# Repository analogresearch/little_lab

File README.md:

# LITTLE████_LAB

DC IN: 6..28 V 

MIDI noch noch nicht implementiert.

MIDI channel und Programm werden über Codierschalter gewählt.
MIDI: Ausnahme Schalter 0 = MIDI channel 16!

Rev.B: Pullups für Coderschalter
Rev.C: Pulldowns für inputs, debugging pads.

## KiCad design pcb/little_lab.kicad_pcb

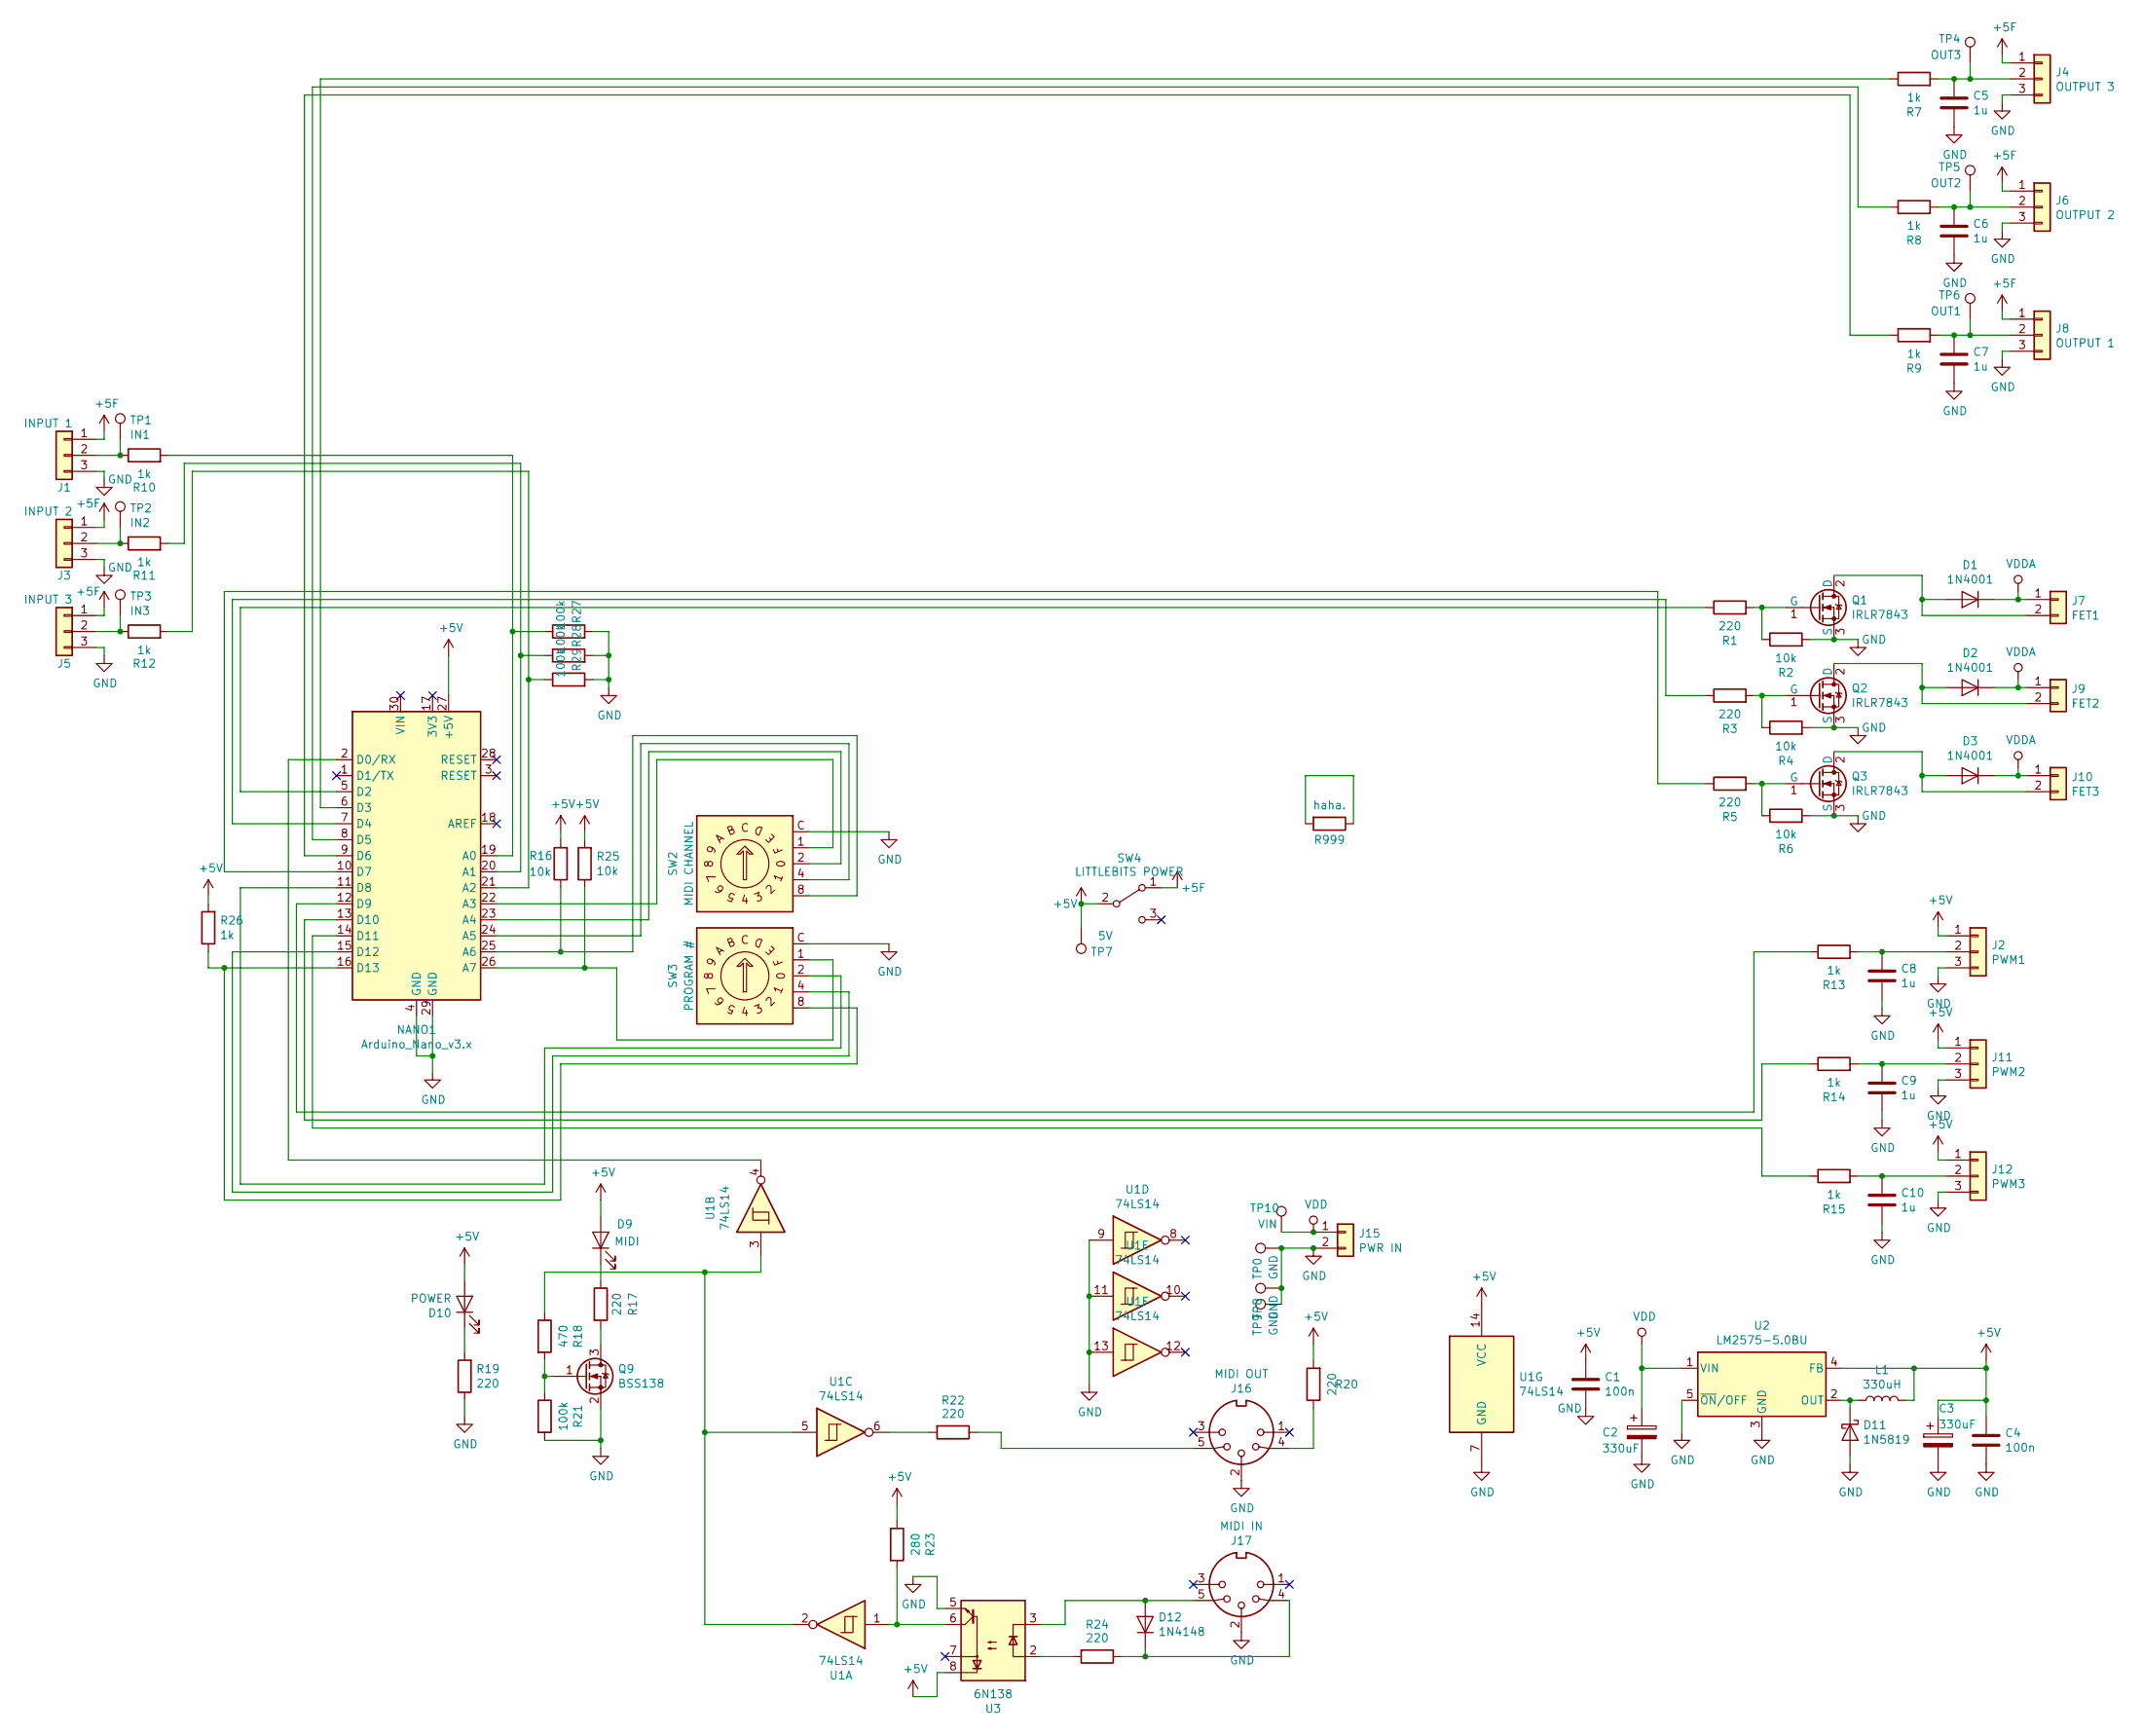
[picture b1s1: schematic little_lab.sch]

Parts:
C1, C4: 100n; C_1206_3216Metric_Pad1.42x1.75mm_HandSolder
C2, C3: 330uF; CP_Elec_10x10
C5, C6, C7, C8, C9, C10: 1u; C_1206_3216Metric_Pad1.42x1.75mm_HandSolder
D1, D2, D3: 1N4001; D_SOD-123F
D9: MIDI; LED_1206_3216Metric_Pad1.42x1.75mm_HandSolder
D10: POWER; LED_1206_3216Metric_Pad1.42x1.75mm_HandSolder
D11: 1N5819; D_SOD-123
D12: 1N4148; D_SOD-123
J1: INPUT 1; bitsnaps_input
J2: PWM1; EK508V-03P
J3: INPUT 2; bitsnaps_input
J4: OUTPUT 3; bitsnaps_output
J5: INPUT 3; bitsnaps_input
J6: OUTPUT 2; bitsnaps_output
J7: FET1; EK508V-02P
J8: OUTPUT 1; bitsnaps_output
J9: FET2; EK508V-02P
J10: FET3; EK508V-02P
J11: PWM2; EK508V-03P
J12: PWM3; EK508V-03P
J15: PWR IN; EK508V-02P
J16: MIDI OUT; MIDI_DIN5
J17: MIDI IN; MIDI_DIN5
L1: 330uH; L_7.3x7.3_Handsoldering
NANO1: Arduino_Nano_v3.x; Arduino_Nano
Q1, Q2, Q3: IRLR7843; TO-252-2
Q9: BSS138; SOT-23
R1, R3, R5, R17, R19, R20, R22, R24: 220; R_1206_3216Metric_Pad1.42x1.75mm_HandSolder
R2, R4, R6, R16, R25: 10k; R_1206_3216Metric_Pad1.42x1.75mm_HandSolder
R7, R8, R9, R10, R11, R12, R13, R14, R15, R26: 1k; R_1206_3216Metric_Pad1.42x1.75mm_HandSolder
R18: 470; R_1206_3216Metric_Pad1.42x1.75mm_HandSolder
R21, R27, R28, R29: 100k; R_1206_3216Metric_Pad1.42x1.75mm_HandSolder
R23: 280; R_1206_3216Metric_Pad1.42x1.75mm_HandSolder
R999: haha.; R_1206_3216Metric_Pad1.42x1.75mm_HandSolder
SW2: MIDI CHANNEL; SA-7050B
SW3: PROGRAM #; SA-7050B
SW4: LITTLEBITS POWER; K3-1235S-K1
TP0: GND; TestPoint_THTPad_D2.0mm_Drill1.0mm
TP1: IN1; TestPoint_THTPad_D2.0mm_Drill1.0mm
TP2: IN2; TestPoint_THTPad_D2.0mm_Drill1.0mm
TP3: IN3; TestPoint_THTPad_D2.0mm_Drill1.0mm
TP4: OUT3; TestPoint_THTPad_D2.0mm_Drill1.0mm
TP5: OUT2; TestPoint_THTPad_D2.0mm_Drill1.0mm
TP6: OUT1; TestPoint_THTPad_D2.0mm_Drill1.0mm
TP7: 5V; TestPoint_THTPad_D2.0mm_Drill1.0mm
TP8, TP9: GND; TestPoint_Pad_4.0x4.0mm
TP10: VIN; TestPoint_THTPad_D2.0mm_Drill1.0mm
U1: 74LS14; SOIC-14_3.9x8.7mm_P1.27mm
U2: LM2575-5.0BU; TO-263-5_TabPin3
U3: 6N138; SMDIP-8_W9.53mm

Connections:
+5F: J1.1, J3.1, J4.1, J5.1, J6.1, J8.1, SW4.1 (A)
+5V: C1.1, C3.1, C4.1, D9.2 (A), D10.2 (A), J2.1, J11.1, J12.1, L1.2, NANO1.27 (+5V), R16.2, R20.2, R23.1, R25.2, R26.2, SW4.2 (B), TP7.1, U1.14 (VCC), U2.4 (FB), U3.8
GND: C1.2, C2.2, C3.2, C4.2, C5.2, C6.2, C7.2, C8.2, C9.2, C10.2, D11.2 (A), J1.3, J2.3, J3.3, J4.3, J5.3, J6.3, J8.3, J11.3, J12.3, J15.2, J16.2, J17.2, NANO1.4 (GND), NANO1.29 (GND), Q1.3 (S), Q2.3 (S), Q3.3 (S), Q9.2 (S), R2.2, R4.2, R6.2, R19.1, R21.2, R27.2, R28.2, R29.2, SW2.C, SW3.C, TP0.1, TP8.1, TP9.1, U1.7 (GND), U1.9, U1.11, U1.13, U2.3 (GND), U2.5 (~ON~/OFF), U3.5
unnamed: C5.1, J4.2, R7.2, TP4.1
unnamed: C6.1, J6.2, R8.2, TP5.1
unnamed: C7.1, J8.2, R9.2, TP6.1
unnamed: C8.1, J2.2, R13.2
unnamed: C9.1, J11.2, R14.2
unnamed: C10.1, J12.2, R15.2
unnamed: D1.2 (A), J7.2, Q1.2 (D)
unnamed: D2.2 (A), J9.2, Q2.2 (D)
unnamed: D3.2 (A), J10.2, Q3.2 (D)
unnamed: D9.1 (K), R17.1
unnamed: D10.1 (K), R19.2
unnamed: D11.1 (K), L1.1, U2.2 (OUT)
unnamed: D12.1 (K), J17.4, R24.1
unnamed: D12.2 (A), J17.5, U3.3
unnamed: J1.2, R10.1, TP1.1
unnamed: J3.2, R11.1, TP2.1
unnamed: J5.2, R12.1, TP3.1
unnamed: J16.4, R20.1
unnamed: J16.5, R22.1
unnamed: NANO1.2 (D0/RX), U1.4
unnamed: NANO1.5 (D2), R1.1
unnamed: NANO1.6 (D3), R7.1
unnamed: NANO1.7 (D4), R3.1
unnamed: NANO1.8 (D5), R8.1
unnamed: NANO1.9 (D6), R9.1
unnamed: NANO1.10 (D7), R5.1
unnamed: NANO1.11 (D8), SW3.2
unnamed: NANO1.12 (D9), R13.1
unnamed: NANO1.13 (D10), R14.1
unnamed: NANO1.14 (D11), R15.1
unnamed: NANO1.15 (D12), SW3.4
unnamed: NANO1.16 (D13), R26.1, SW3.8
unnamed: NANO1.19 (A0), R10.2, R27.1
unnamed: NANO1.20 (A1), R11.2, R28.1
unnamed: NANO1.21 (A2), R12.2, R29.1
unnamed: NANO1.22 (A3), SW2.1
unnamed: NANO1.23 (A4), SW2.2
unnamed: NANO1.24 (A5), SW2.4
unnamed: NANO1.25 (A6), R16.1, SW2.8
unnamed: NANO1.26 (A7), R25.1, SW3.1
unnamed: Q1.1 (G), R1.2, R2.1
unnamed: Q2.1 (G), R3.2, R4.1
unnamed: Q3.1 (G), R5.2, R6.1
unnamed: Q9.1 (G), R18.2, R21.1
unnamed: Q9.3 (D), R17.2
unnamed: R18.1, U1.2, U1.3, U1.5
unnamed: R22.2, U1.6
unnamed: R23.2, U1.1, U3.6
unnamed: R24.2, U3.2
unnamed: R999.1, R999.2
VDD: C2.1, J15.1, TP10.1, U2.1 (VIN)
VDDA: D1.1 (K), D2.1 (K), D3.1 (K), J7.1, J9.1, J10.1

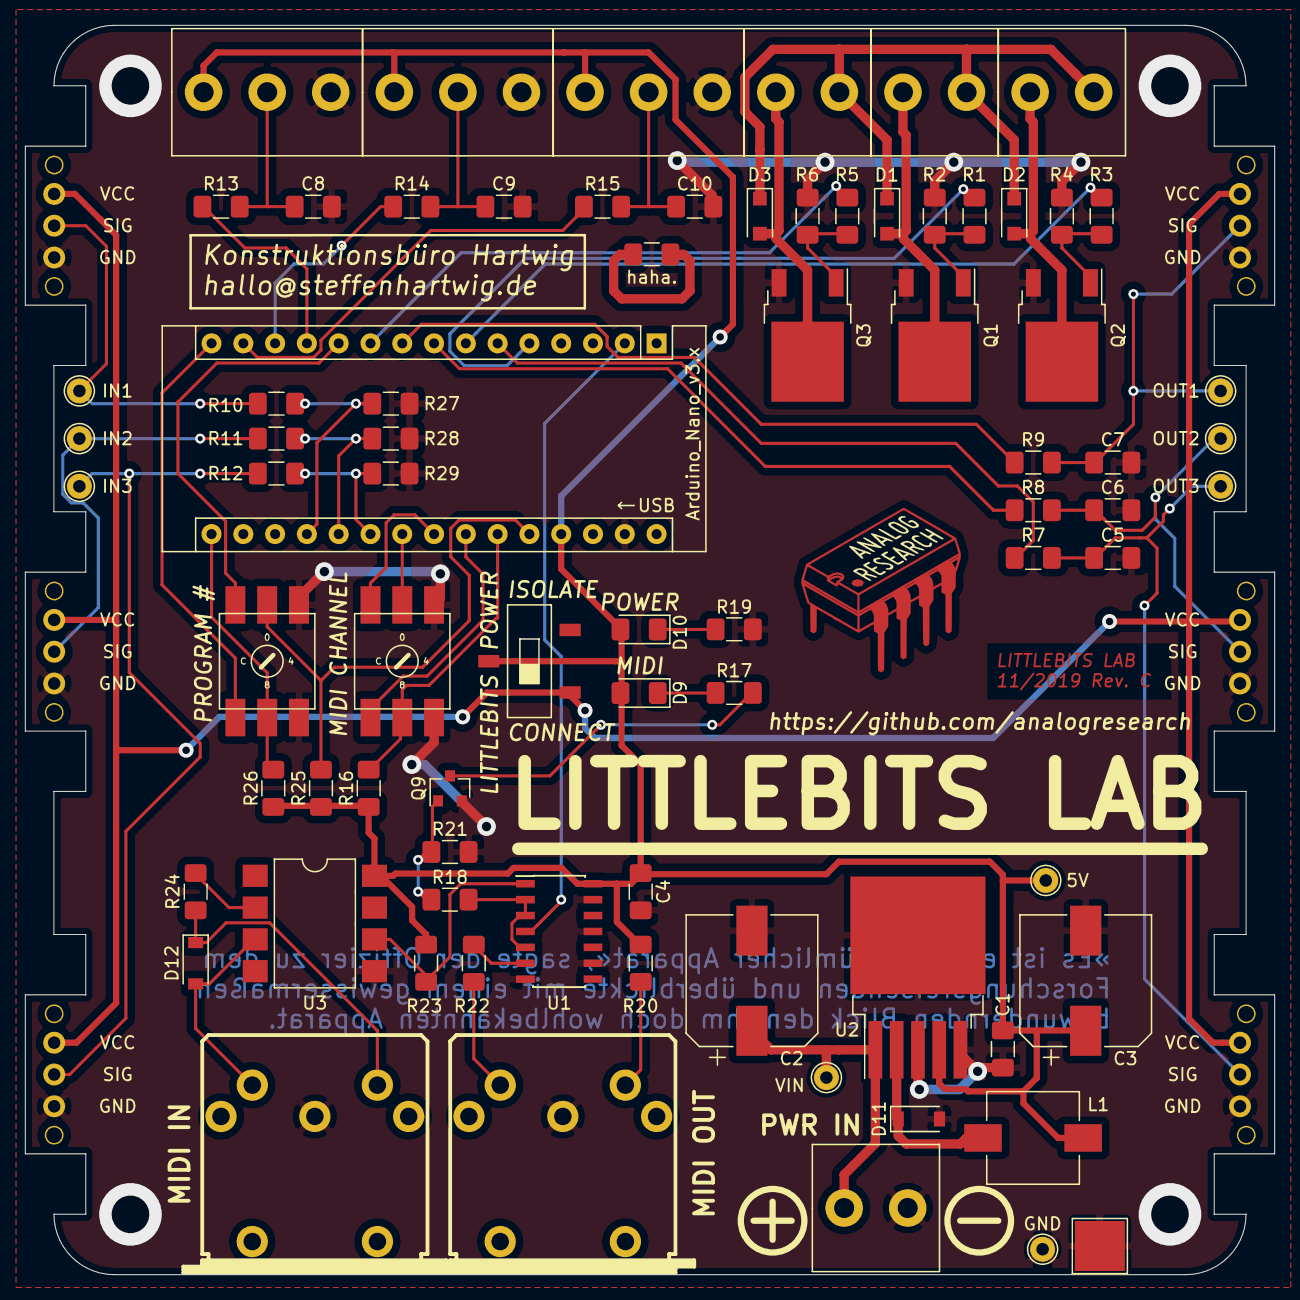
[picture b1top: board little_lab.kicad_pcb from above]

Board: 2 copper layers, 99.8 x 99.8 mm, 86 parts (1 on the bottom side), 55 nets.

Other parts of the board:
Ref**: Val**; logo-analogresearch-16mm

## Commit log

2020-02-11 Create little_lab-brd.svg
    adding brd svg
2020-04-28 Update little_lab.ino
    testprogramm update
2020-05-06 gitignore fix
2020-12-02 added pcb layout
